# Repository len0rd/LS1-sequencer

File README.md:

# LS1-sequencer
Modular analog synth/8 step sequencer

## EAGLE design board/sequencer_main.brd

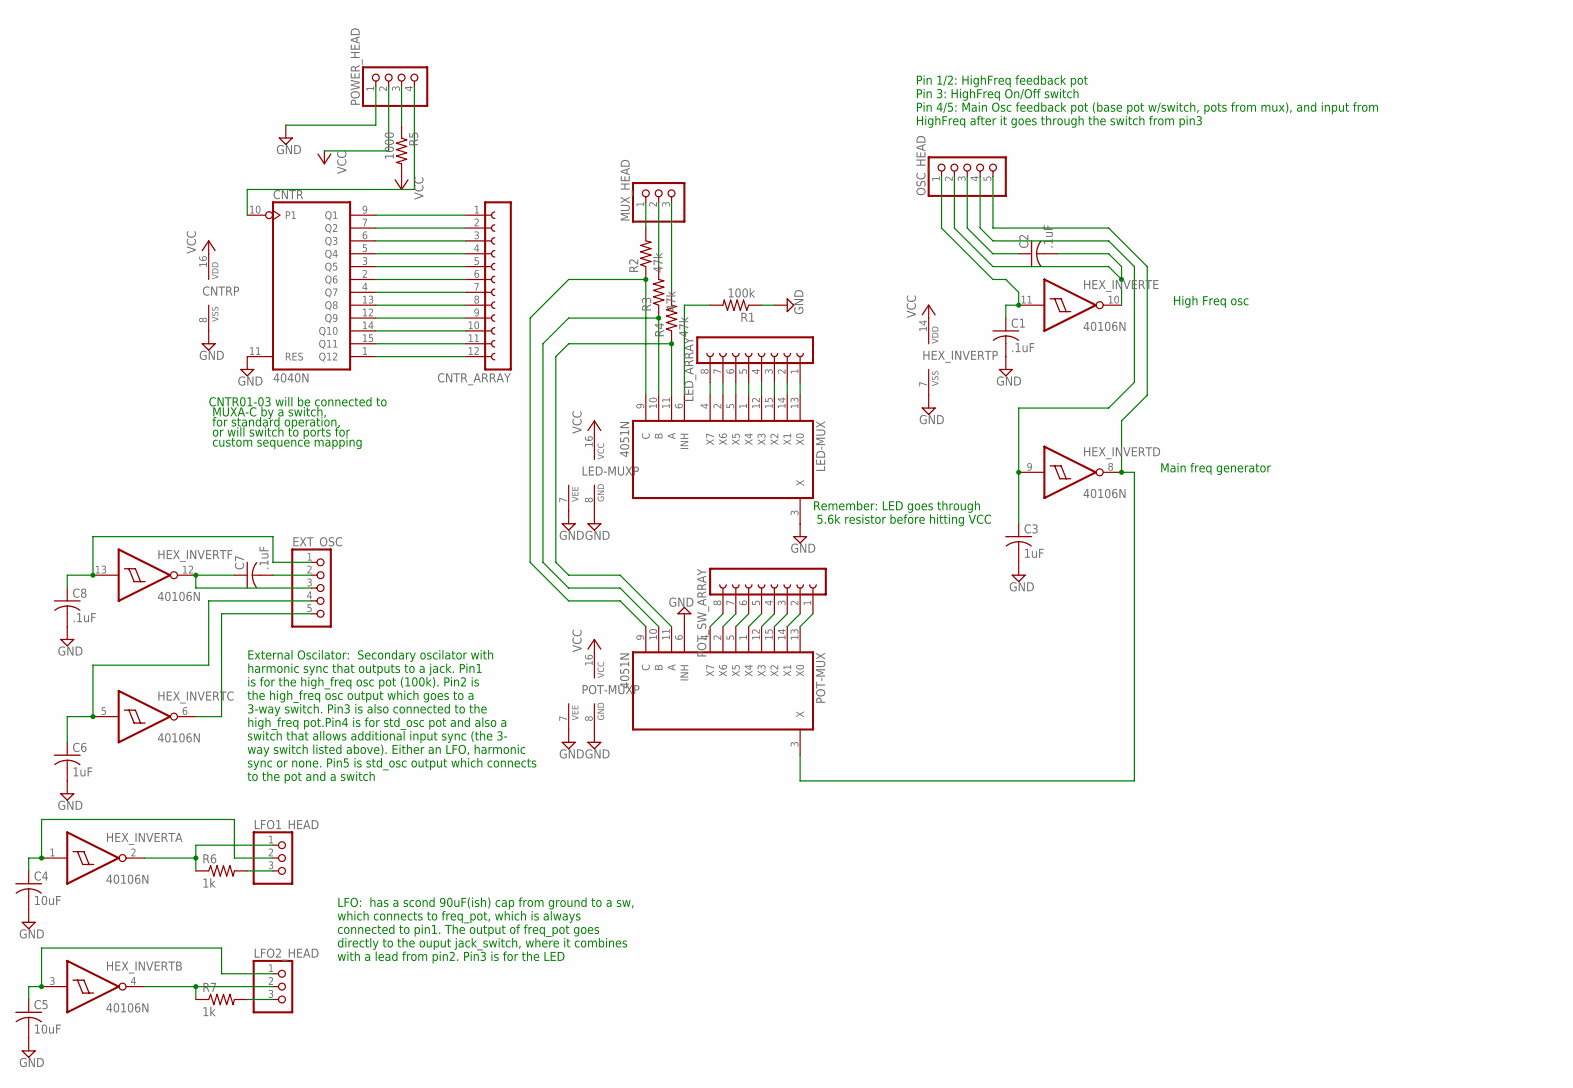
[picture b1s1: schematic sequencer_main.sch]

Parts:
C1, C2, C7, C8: .1uF; C025-025X050
C3, C6: 1uF; C025-025X050
C4, C5: 10uF; C025-025X050
CNTR: 4040N; DIL16
CNTR_ARRAY: FE12-1; FE12
EXT_OSC: PINHD-1X5; 1X05
HEX_INVERT: 40106N; DIL14
LED-MUX: 4051N; DIL16
LED_ARRAY: FE08-1; FE08
LFO1_HEAD, LFO2_HEAD: PINHD-1X3; 1X03
MUX_HEAD: PINHD-1X3; 1X03
OSC_HEAD: PINHD-1X5; 1X05
POT-MUX: 4051N; DIL16
POT_SW_ARRAY: FE08-1; FE08
POWER_HEAD: PINHD-1X4; 1X04
R1: 100k; 0204/7
R2, R3, R4: 47k; 0204/7
R5: 1000; 0204/7
R6, R7: 1k; 0204/7

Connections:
GND: C1.2, C3.2, C4.2, C5.2, C6.2, C8.2, CNTR.8 (VSS), CNTR.11 (RES), HEX_INVERT.7 (VSS), LED-MUX.3 (X), LED-MUX.7 (VEE), LED-MUX.8 (GND), POT-MUX.6 (INH), POT-MUX.7 (VEE), POT-MUX.8 (GND), POWER_HEAD.1, R1.1
unnamed: LED-MUX.13 (X0), LED_ARRAY.1
unnamed: LED-MUX.14 (X1), LED_ARRAY.2
unnamed: LED-MUX.15 (X2), LED_ARRAY.3
unnamed: LED-MUX.12 (X3), LED_ARRAY.4
unnamed: LED-MUX.1 (X4), LED_ARRAY.5
unnamed: LED-MUX.5 (X5), LED_ARRAY.6
unnamed: LED-MUX.2 (X6), LED_ARRAY.7
unnamed: LED-MUX.4 (X7), LED_ARRAY.8
unnamed: LED-MUX.9 (C), POT-MUX.9 (C), R2.1
unnamed: LED-MUX.10 (B), POT-MUX.10 (B), R3.1
unnamed: LED-MUX.11 (A), POT-MUX.11 (A), R4.1
unnamed: CNTR.10 (P1), POWER_HEAD.4
unnamed: CNTR.9 (Q1), CNTR_ARRAY.1
unnamed: CNTR.7 (Q2), CNTR_ARRAY.2
unnamed: CNTR.6 (Q3), CNTR_ARRAY.3
unnamed: CNTR.5 (Q4), CNTR_ARRAY.4
unnamed: CNTR.3 (Q5), CNTR_ARRAY.5
unnamed: CNTR.2 (Q6), CNTR_ARRAY.6
unnamed: CNTR.4 (Q7), CNTR_ARRAY.7
unnamed: CNTR.1 (Q12), CNTR_ARRAY.12
unnamed: CNTR.15 (Q11), CNTR_ARRAY.11
unnamed: CNTR.14 (Q10), CNTR_ARRAY.10
unnamed: CNTR.12 (Q9), CNTR_ARRAY.9
unnamed: CNTR.13 (Q8), CNTR_ARRAY.8
unnamed: MUX_HEAD.1, R2.2
unnamed: MUX_HEAD.2, R3.2
unnamed: MUX_HEAD.3, R4.2
unnamed: LED-MUX.6 (INH), R1.2
unnamed: POT-MUX.4 (X7), POT_SW_ARRAY.8
unnamed: POT-MUX.2 (X6), POT_SW_ARRAY.7
unnamed: POT-MUX.5 (X5), POT_SW_ARRAY.6
unnamed: POT-MUX.1 (X4), POT_SW_ARRAY.5
unnamed: POT-MUX.12 (X3), POT_SW_ARRAY.4
unnamed: POT-MUX.15 (X2), POT_SW_ARRAY.3
unnamed: POT-MUX.14 (X1), POT_SW_ARRAY.2
unnamed: POT-MUX.13 (X0), POT_SW_ARRAY.1
unnamed: POWER_HEAD.3, R5.1
unnamed: C3.1, HEX_INVERT.9 (I), OSC_HEAD.4
unnamed: C1.1, HEX_INVERT.11 (I), OSC_HEAD.1
unnamed: C2.2, HEX_INVERT.10 (O), OSC_HEAD.2
unnamed: HEX_INVERT.8 (O), OSC_HEAD.5, POT-MUX.3 (X)
unnamed: C7.2, EXT_OSC.2
unnamed: HEX_INVERT.2 (O), LFO1_HEAD.1, R6.1
unnamed: LFO1_HEAD.3, R6.2
unnamed: C4.1, HEX_INVERT.1 (I), LFO1_HEAD.2
unnamed: HEX_INVERT.4 (O), LFO2_HEAD.2, R7.1
unnamed: C5.1, HEX_INVERT.3 (I), LFO2_HEAD.1
unnamed: LFO2_HEAD.3, R7.2
unnamed: C2.1, OSC_HEAD.3
unnamed: C8.1, EXT_OSC.1, HEX_INVERT.13 (I)
unnamed: C6.1, EXT_OSC.4, HEX_INVERT.5 (I)
unnamed: C7.1, EXT_OSC.3, HEX_INVERT.12 (O)
unnamed: EXT_OSC.5, HEX_INVERT.6 (O)
VCC: CNTR.16 (VDD), HEX_INVERT.14 (VDD), LED-MUX.16 (VCC), POT-MUX.16 (VCC), POWER_HEAD.2, R5.2

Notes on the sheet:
CNTR01-03 will be connected to MUXA-C by a switch, for standard operation, or will switch to ports for custom sequence mapping
LFO: has a scond 90uF(ish) cap from ground to a sw, which connects to freq_pot, which is always connected to pin1. The output of freq_pot goes directly to the ouput jack_switch, where it combines with a lead from pin2. Pin3 is for the LED
External Oscilator: Secondary oscilator with harmonic sync that outputs to a jack. Pin1 is for the high_freq osc pot (100k). Pin2 is the high_freq osc output which goes to a 3-way switch. Pin3 is also connected to the high_freq pot.Pin4 is for std_osc pot and also a switch that allows additional in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
Main freq generator
Remember: LED goes through 5.6k resistor before hitting VCC
High Freq osc
Pin 1/2: HighFreq feedback pot Pin 3: HighFreq On/Off switch Pin 4/5: Main Osc feedback pot (base pot w/switch, pots from mux), and input from HighFreq after it goes through the switch from pin3

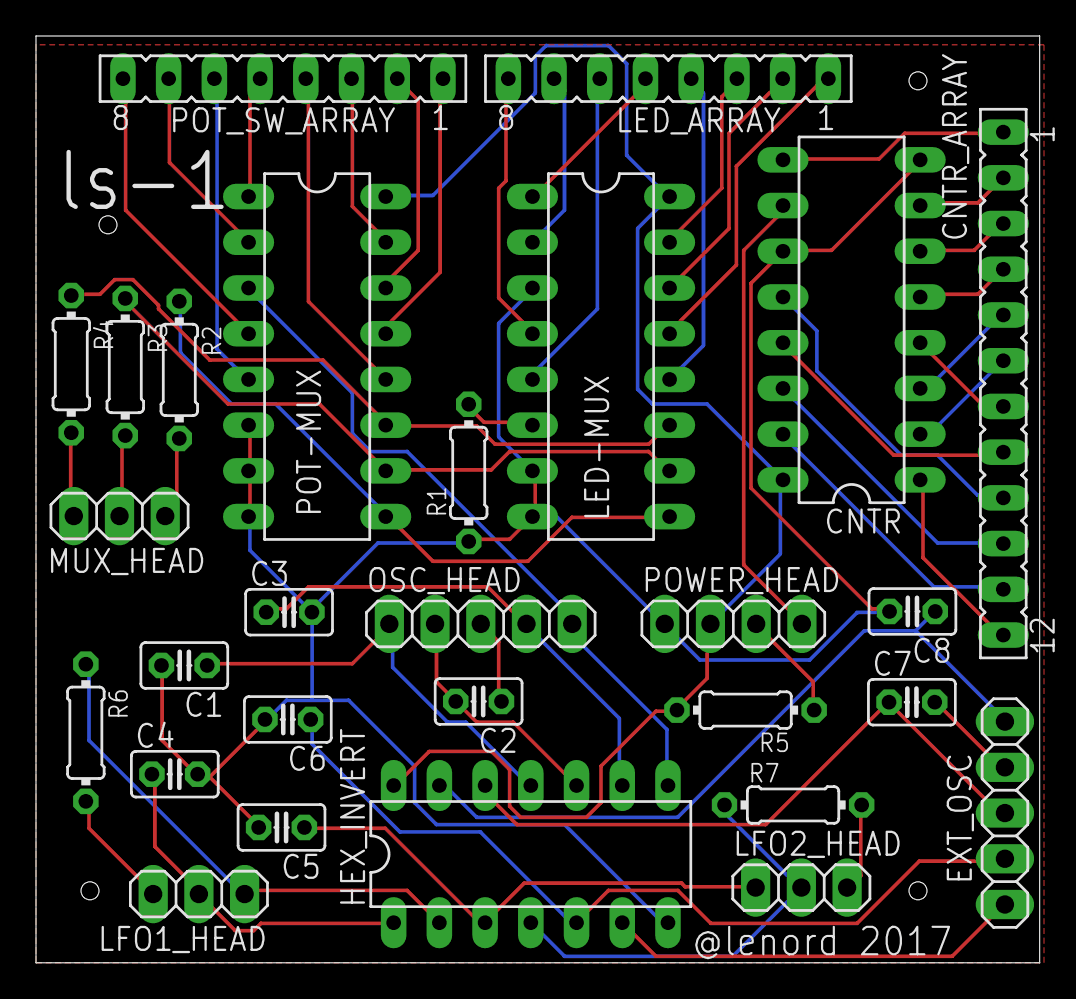
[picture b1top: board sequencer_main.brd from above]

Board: 2 copper layers, 55.8 x 51.5 mm, 28 parts (0 on the bottom side), 55 nets.

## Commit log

2017-07-17 Initial file commit, need to update board and add schematic immediately as these are older versions
2017-07-17 Added the proper board/schematic files for the circuit board. Inventor case files need to be rebuilt because inventor is stupid
2017-07-21 Added a gitignore. Added some datasheets for the components I'm planning to use. Almost done rebuilding the case inventor file(since I was an idiot and lost the original, completed one...)
2017-07-21 twas a struggle, but I finished the main case sheet sketch and got it to extrude properly
2017-07-21 Changed some of the through-holes to be filleted rectangles to allow less percision in assembley
2017-07-21 Added dxf file export of top face for use on waterjet
2017-07-26 Re-exported topFace as a 2004 dxf for compatability. Also added an stp version of the part since I was stupid and used 2018 Inventor before thinking about backwards compatability...
2017-07-26 Made side and back face height slightly lower than the front panel for when I add the top/lid plate. Re-exported stp version. Re-exported the dxf with an EVEN lower compatability version(2000)
2017-08-04 added an illustrator file with the dxf of the case. i plan on adding some text to this as a layout for however I discover the best way to get it on there is...
2017-08-13 Added mux spec doc
2017-08-13 Finished the frontface text decal thing. Think I'll probably get this printed as a vinyl decal and see how that works
